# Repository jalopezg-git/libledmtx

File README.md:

# libledmtx: a library to drive LED dot-matrix displays written in PIC18 assembler

## Introduction
The libledmtx project was developed as a subproject of [p18clock](https://github.com/jalopezg-git/p18clock).
The library is completely written in PIC18 assembler and follows the call convention of the [SDCC](http://sdcc.sourceforge.net/) pic16 port.
Exported routines are meant to be called in by C code.
If you intend to issue calls from assembler, make sure that you follow the [pic16 port](http://sdcc.sourceforge.net/doc/sdccman.pdf) call convention.

## Building libledmtx
Before compiling the library make sure you have this installed:
- [gputils](https://gputils.sourceforge.io/) (the GNU PIC utilities), providing an assembler, librarian, and linker
- GNU make
- GNU gettext-runtime (provides `envsubst`)

To build libledmtx change to the directory where you extracted libledmtx and type
```bash
$ make

# To also compile the included examples
$ cd examples/
$ make
````

### Optional features
Additional features can be enabled / disabled by appending a list of `ENABLE_xxx=(0|1)` to the make command line, e.g. to build libledmtx with support for double buffer

```bash
$ make ENABLE_DOUBLE_BUFFER=1
```

#### Double buffer
libledmtx can be optionally built to support double buffer configuration.  To do so, you can append `ENABLE_DOUBLE_BUFFER=1` to the make command line.
Note that, in a double-buffer build, both the frontbuffer and backbuffer point to the same buffer by default.  See [`ledmtx_setbackbuffer()`](https://github.com/jalopezg-git/libledmtx/blob/master/include/ledmtx_core.h#L191) for details.

The feature is disabled by default.  Enabling it uses +4 additional bytes of RAM and makes each library function that touches a buffer +2 cycles slower, including the driver's vertical refresh routine.
This is, in general, acceptable for most applications though.

#### User-defined viewport
Set `ENABLE_VIEWPORT=1` to build a viewport-aware version of libledmtx, i.e. enable support for having a framebuffer larger than the physical display.
In this case, `libledmtx_init()` sets both, the framebuffer and initial viewport geometry.  The visible rectangle can be set as many times as needed via [`ledmtx_setviewport()`](https://github.com/jalopezg-git/libledmtx/blob/master/include/ledmtx_core.h#L147).

This feature is disabled by default.  When enabled, it uses +4 additional bytes of RAM in the access bank and makes the driver vertical refresh routine slightly slower (~5 cycles).

## Testing
The test suite is based on LLVM's lit.  Besides the dependencies required to build libledmtx, running tests also requires:
- llvm (provides `lit`)
- SDCC
- gpsim (The GNUPIC Simulator)

Tests can be simply run as follows:
```bash
$ lit tests/
```

## Installing
To install required files, change to the directory where you cloned libledmtx and run `make install` setting `INSTALL_PREFIX` to the destination directory, e.g.
```bash
$ make INSTALL_PREFIX=$HOME/.local/libledmtx/ install
```

## Hardware
Refer to docs and KiCad schematic design in the [hardware](https://github.com/jalopezg-git/libledmtx/tree/master/hardware/) directory.
The r393c164 driver requires a `ledmtx_r393c164.inc` configuration file that specifies which I/O port and pins to use for each output signal.
The used I/O port still should be manually configured writing to the `TRISx` / `ADCON1` registers.

## Examples
Some minimal examples are available in the [examples](https://github.com/jalopezg-git/libledmtx/tree/master/examples/) directory.
- [hello32x7](https://github.com/jalopezg-git/libledmtx/blob/master/examples/hello32x7/hello32x7.c), a simple program that prints "hello" using `printf()` (via the `STREAM_USER` stdio stream).
- [scrollstr32x7](https://github.com/jalopezg-git/libledmtx/blob/master/examples/scrollstr32x7/scrollstr32x7.c), that exercises the scrollstr module to asynchronously scroll a long text.

## How does it work?
libledmtx reserves part of the device's RAM as video memory (framebuffer).  The framebuffer is encoded left to right, top to bottom, 1bpp, i.e. each byte holds the value of 8 pixels.
The library has two distinct parts: a set of routines that alter the contents of the framebuffer, and the 'driver', which periodically reads (parts of) the framebuffer and changes the state of the appropriate MCU I/O pins in order to drive the simple video hardware (see [Hardware](https://github.com/jalopezg-git/libledmtx/#hardware)).
The driver is usually activated as part of the libledmtx interrupt service routine (ISR).

For the sake of efficiency, libledmtx tries to avoid using the `BSR` register where possible; thus, frequently accessed data is kept in the Access Bank.
Note that neither SDCC nor libledmtx support the PIC18 Extended Instruction Set (XINST).

libledmtx offers a [core](https://github.com/jalopezg-git/libledmtx/blob/master/include/ledmtx_core.h) set of routines (e.g. `ledmtx_putpixel()`, `ledmtx_setfont()`, or `ledmtx_putchar()`), and a set of modules that can be optionally linked in order to extend the core's capabilities.  Specifically, the following modules are supported:
- `scrollstr`: helper for character string scroll.  Allows automatic scroll of up to 8 strings from the ISR (see [`ledmtx_scrollstr_start()`](https://github.com/jalopezg-git/libledmtx/blob/master/include/ledmtx_scrollstr.h)).
- `perf`: measures time taken to service the libledmtx interrupt.

As of june 2024, libledmtx can work with multiple buffers (experimental).  In this configuration, the driver reads from the frontbuffer, whereas the framebuffer manipulation routines act on the backbuffer.  Once the backbuffer is ready, buffers can be swapped by using `ledmtx_swapbuffers()`.
In this case, buffers are pointed to by `ledmtx_frontbuffer` and `ledmtx_backbuffer`.  Given the additional level of indirection, all routines that need to load buffer addresses had the `lfsr` instruction replaced by two `movff` instructions, making them two cycles slower.  This overhead is, in general, acceptable for most of the purposes.

The addition of this feature also allows for changing the viewport, i.e. having a framebuffer larger than the actual display and only making part of it visible (TBD).

## Issues / limits
core:
- Maximum framebuffer size:	255x255
- Maximum size of a character:		8x255 (greater than VGA 8x14 is probably useless?)

r393c164 driver:
- High row count most probably looks dimmed, due to multiplexing.

scrollstr module:
- Auto-scroll vector capacity:		8 entries
- Maximum string length:		128 chars (including `\0`)

## Notes on linking against libledmtx
This section provides general guidelines to use and link libledmtx in your project.

1. Copy [`Makefile.template`](https://github.com/jalopezg-git/libledmtx/blob/master/doc/Makefile.template) to you project directory and tune it.
In particular, the value of the `P18FXXX`, `LIBDIR`, `INCLUDEDIR`, `O` and `modules` variables should be set accordingly.
`LIBDIR` and `INCLUDEDIR` should point to the libledmtx install directories.
`O` and `MODULES` list additional libledmtx objects and/or libraries that should be linked.
The `OBJECTS +=` line should list your project object files.

2. Write configuration file for the driver.
For the r393c164 driver, the file `ledmtx_r393c164.inc` (located in your project's directory), should look like this.  The I/O port and pins should be changed to reflect your wiring.
```
  LEDMTX_R393C164_IOPORT	equ	PORTA
  LEDMTX_R393C164_RCLK		equ	RA0
  LEDMTX_R393C164_RRST		equ	RA1
  LEDMTX_R393C164_RENA		equ	RA2
  LEDMTX_R393C164_CCLK		equ	RA3
  LEDMTX_R393C164_CDAT		equ	RA4
```

3. The `LEDMTX_BEGIN_MODULES_INIT` / `LEDMTX_END_MODULES_INIT` section is mandatory even if you are not using any module.
Header files for any module should be `#include`d before `ledmtx_core.h`.
A framebuffer (i.e., a small data memory area that stores the current frame) should be declared as follows:
```c
  LEDMTX_DECLARE_FRAMEBUFFER(_width, _height)
```
where `_width` and `_height` must be constant expressions.

4. If you are using TMR0 interrupts to call the driver-specific routine for vertical refresh, you should also include the following code:
```c
  DEF_INTLOW(low_int)
  DEF_HANDLER(SIG_TMR0, _tmr0_handler)
  END_DEF

  SIGHANDLERNAKED(_tmr0_handler)
  {
    LEDMTX_BEGIN_ISR
    LEDMTX_VERTREFRESH
    LEDMTX_END_ISR
  }
```

5. `ledmtx_init()` should be called before calling any other libledmtx function.
If Timer0 is used to drive the display (recommended), proper values for the `tmr0h`, `tmr0l`, and `t0con` paramaters have to be passed.
The `ledmtx_modegen` utility included in [support/](https://github.com/jalopezg-git/libledmtx/tree/master/support/) automates this task.
If you are using the provided `Makefile.template`, `ledmtx_modegen_modes.h` shall be automatically generated from the provided values.  Because the `LEDMTX__DEFAULT_xxx` preprocessor macros are also defined in the abovementioned header, the call to `ledmtx_init()` may just become:
```c
#include "ledmtx_modegen_modes.h"
// ...

ledmtx_init(LEDMTX_INIT_CLEAR | LEDMTX_INIT_TMR0,
	    LEDMTX__DEFAULT_WIDTH, LEDMTX__DEFAULT_HEIGHT,
	    LEDMTX__DEFAULT_TMR0H, LEDMTX__DEFAULT_TMR0L, LEDMTX__DEFAULT_T0CON);
```

## Contributing
Contributions either in the form of new features / fixes, hardware improvements, or documentation are welcome :+1:.
Feel free to open a pull request if you have something to say!

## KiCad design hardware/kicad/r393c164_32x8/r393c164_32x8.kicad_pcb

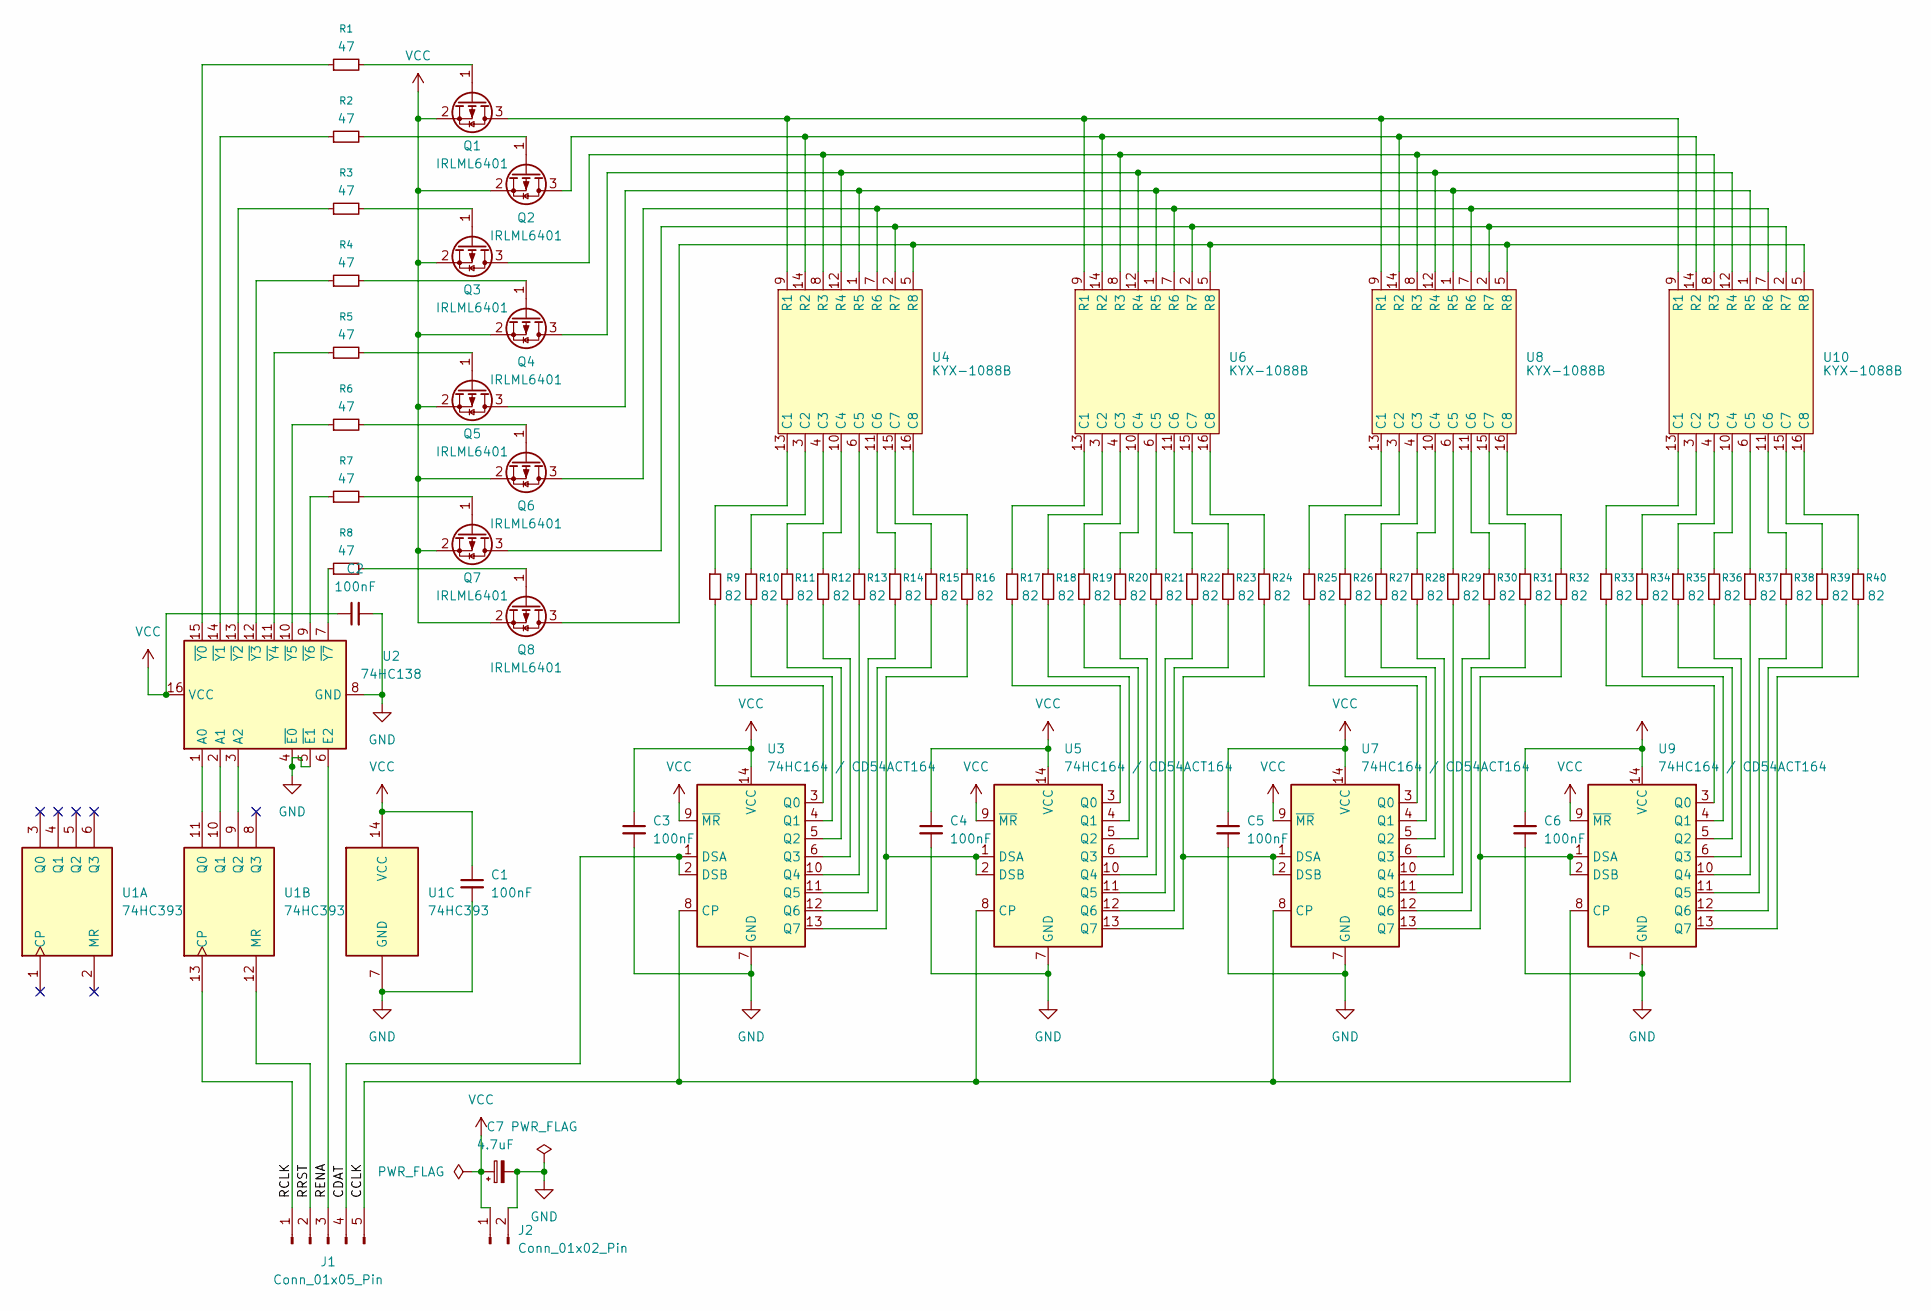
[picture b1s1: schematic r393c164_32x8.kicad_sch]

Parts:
C1, C2, C3, C4, C5, C6: 100nF; C_1206_3216Metric_Pad1.33x1.80mm_HandSolder
C7: 4.7uF; CP_Radial_D4.0mm_P2.00mm
J1: Conn_01x05_Pin; PinHeader_1x05_P2.54mm_Vertical
J2: Conn_01x02_Pin; PinHeader_1x02_P2.54mm_Vertical
Q1, Q2, Q3, Q4, Q5, Q6, Q7, Q8: IRLML6401; SOT-23
R1, R2, R3, R4, R5, R6, R7, R8: 47; R_0805_2012Metric_Pad1.20x1.40mm_HandSolder
R9, R10, R11, R12, R13, R14, R15, R16, R17, R18, R19, R20, R21, R22, R23, R24, R25, R26, R27, R28, R29, R30, R31, R32, R33, R34, R35, R36, R37, R38, R39, R40: 82; R_0805_2012Metric_Pad1.20x1.40mm_HandSolder
U1: 74HC393; SOIC-14_3.9x8.7mm_P1.27mm
U2: 74HC138; SOIC-16_3.9x9.9mm_P1.27mm
U3, U5, U7, U9: 74HC164 / CD54ACT164; SOIC-14_3.9x8.7mm_P1.27mm
U4, U6, U8, U10: KYX-1088B; KYX-1088AB

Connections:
/CCLK: J1.5, U3.8 (CP), U5.8 (CP), U7.8 (CP), U9.8 (CP)
/CDAT: J1.4, U3.1 (DSA), U3.2 (DSB)
/RCLK: J1.1, U1.13 (CP)
/RENA: J1.3, U2.6 (E2)
/RRST: J1.2, U1.12 (MR)
GND: C1.2, C2.2, C3.2, C4.2, C5.2, C6.2, C7.2, J2.2, U1.7 (GND), U2.4 (~E0), U2.5 (~E1), U2.8 (GND), U3.7 (GND), U5.7 (GND), U7.7 (GND), U9.7 (GND)
unnamed: Q1.3 (D), U4.9 (R1), U6.9 (R1), U8.9 (R1), U10.9 (R1)
unnamed: Q1.1 (G), R1.2
unnamed: Q2.3 (D), U4.14 (R2), U6.14 (R2), U8.14 (R2), U10.14 (R2)
unnamed: Q2.1 (G), R2.2
unnamed: Q3.3 (D), U4.8 (R3), U6.8 (R3), U8.8 (R3), U10.8 (R3)
unnamed: Q3.1 (G), R3.2
unnamed: Q4.3 (D), U4.12 (R4), U6.12 (R4), U8.12 (R4), U10.12 (R4)
unnamed: Q4.1 (G), R4.2
unnamed: Q5.3 (D), U4.1 (R5), U6.1 (R5), U8.1 (R5), U10.1 (R5)
unnamed: Q5.1 (G), R5.2
unnamed: Q6.3 (D), U4.7 (R6), U6.7 (R6), U8.7 (R6), U10.7 (R6)
unnamed: Q6.1 (G), R6.2
unnamed: Q7.3 (D), U4.2 (R7), U6.2 (R7), U8.2 (R7), U10.2 (R7)
unnamed: Q7.1 (G), R7.2
unnamed: Q8.3 (D), U4.5 (R8), U6.5 (R8), U8.5 (R8), U10.5 (R8)
unnamed: Q8.1 (G), R8.2
unnamed: U1.11 (Q0), U2.1 (A0)
unnamed: U1.10 (Q1), U2.2 (A1)
unnamed: U1.9 (Q2), U2.3 (A2)
unnamed: R1.1, U2.15 (~Y0)
unnamed: R2.1, U2.14 (~Y1)
unnamed: R3.1, U2.13 (~Y2)
unnamed: R4.1, U2.12 (~Y3)
unnamed: R5.1, U2.11 (~Y4)
unnamed: R6.1, U2.10 (~Y5)
unnamed: R7.1, U2.9 (~Y6)
unnamed: R8.1, U2.7 (~Y7)
unnamed: R9.2, U3.3 (Q0)
unnamed: R10.2, U3.4 (Q1)
unnamed: R11.2, U3.5 (Q2)
unnamed: R12.2, U3.6 (Q3)
unnamed: R13.2, U3.10 (Q4)
unnamed: R14.2, U3.11 (Q5)
unnamed: R15.2, U3.12 (Q6)
unnamed: R16.2, U3.13 (Q7), U5.1 (DSA), U5.2 (DSB)
unnamed: R9.1, U4.13 (C1)
unnamed: R10.1, U4.3 (C2)
unnamed: R11.1, U4.4 (C3)
unnamed: R12.1, U4.10 (C4)
unnamed: R13.1, U4.6 (C5)
unnamed: R14.1, U4.11 (C6)
unnamed: R15.1, U4.15 (C7)
unnamed: R16.1, U4.16 (C8)
unnamed: R17.2, U5.3 (Q0)
unnamed: R18.2, U5.4 (Q1)
unnamed: R19.2, U5.5 (Q2)
unnamed: R20.2, U5.6 (Q3)
unnamed: R21.2, U5.10 (Q4)
unnamed: R22.2, U5.11 (Q5)
unnamed: R23.2, U5.12 (Q6)
unnamed: R24.2, U5.13 (Q7), U7.1 (DSA), U7.2 (DSB)
unnamed: R17.1, U6.13 (C1)
unnamed: R18.1, U6.3 (C2)
unnamed: R19.1, U6.4 (C3)
unnamed: R20.1, U6.10 (C4)
unnamed: R21.1, U6.6 (C5)
unnamed: R22.1, U6.11 (C6)
unnamed: R23.1, U6.15 (C7)
unnamed: R24.1, U6.16 (C8)
unnamed: R25.2, U7.3 (Q0)
unnamed: R26.2, U7.4 (Q1)
unnamed: R27.2, U7.5 (Q2)
unnamed: R28.2, U7.6 (Q3)
unnamed: R29.2, U7.10 (Q4)
unnamed: R30.2, U7.11 (Q5)
unnamed: R31.2, U7.12 (Q6)
unnamed: R32.2, U7.13 (Q7), U9.1 (DSA), U9.2 (DSB)
unnamed: R25.1, U8.13 (C1)
unnamed: R26.1, U8.3 (C2)
unnamed: R27.1, U8.4 (C3)
unnamed: R28.1, U8.10 (C4)
unnamed: R29.1, U8.6 (C5)
unnamed: R30.1, U8.11 (C6)
unnamed: R31.1, U8.15 (C7)
unnamed: R32.1, U8.16 (C8)
unnamed: R33.2, U9.3 (Q0)
unnamed: R34.2, U9.4 (Q1)
unnamed: R35.2, U9.5 (Q2)
unnamed: R36.2, U9.6 (Q3)
unnamed: R37.2, U9.10 (Q4)
unnamed: R38.2, U9.11 (Q5)
unnamed: R39.2, U9.12 (Q6)
unnamed: R40.2, U9.13 (Q7)
unnamed: R33.1, U10.13 (C1)
unnamed: R34.1, U10.3 (C2)
unnamed: R35.1, U10.4 (C3)
unnamed: R36.1, U10.10 (C4)
unnamed: R37.1, U10.6 (C5)
unnamed: R38.1, U10.11 (C6)
unnamed: R39.1, U10.15 (C7)
unnamed: R40.1, U10.16 (C8)
VCC: C1.1, C2.1, C3.1, C4.1, C5.1, C6.1, C7.1, J2.1, Q1.2 (S), Q2.2 (S), Q3.2 (S), Q4.2 (S), Q5.2 (S), Q6.2 (S), Q7.2 (S), Q8.2 (S), U1.14 (VCC), U2.16 (VCC), U3.9 (~MR), U3.14 (VCC), U5.9 (~MR), U5.14 (VCC), U7.9 (~MR), U7.14 (VCC), U9.9 (~MR), U9.14 (VCC)

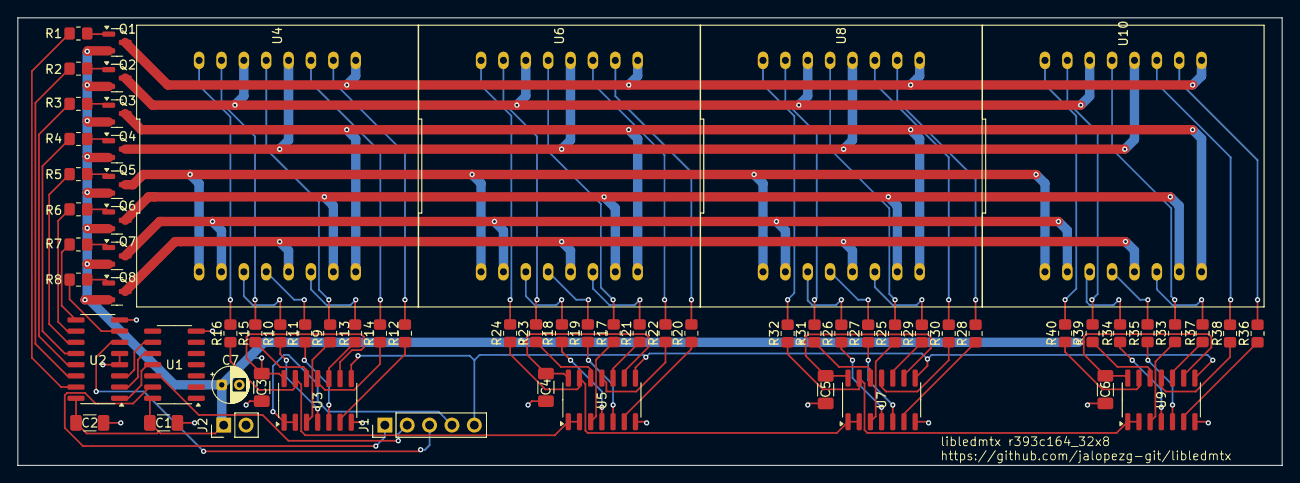
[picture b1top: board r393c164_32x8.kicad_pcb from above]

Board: 2 copper layers, 143.5 x 50.8 mm, 67 parts (0 on the bottom side), 98 nets.

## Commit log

2011-09-01 Legacy version of libledmtx, imported from old repository location
2011-09-01 Minor fix in README.md
2023-09-12 Improve documentation for files in `src/driver/`
2023-09-12 Improve documentation for files in `src/core/`
2023-09-12 Improve documentation for files in `src/font/`
2023-09-12 Improve documentation for files in `src/modules/`
2023-09-12 Improve documentation for files in `include/`
2023-09-12 Minor readability improvements on `ledmtx_tmr0config.c`
2023-09-12 Improve documentation for files in `examples/`
2023-09-12 Rename `ledmtx_scrollstr_s` to `ledmtx_scrollstr_desc`
2023-09-14 Check for `STACK_MODEL_LARGE` PP macro instead (unsupported)
2023-09-14 Add `--use-non-free` to CFLAGS
2023-10-25 Update COPYING (GNU Lesser GPL)
2024-04-08 README.md: add `How does it work?` section
2024-05-21 Add `.gitignore`
2024-05-24 Transition from `p18fxxx.inc` to `ledmtx_config.h`
    Deprecate `src/p18fxxx.inc` generated by make during build
    in favor of `include/ledmtx_config.h`, which contains additional
    information regarding the build.
    It is foreseen to include information regarding upcoming optional
    features, e.g. `LEDMTX_HAVE_DOUBLE_BUFFER`.
2024-05-24 [make.mk] Rename `AFLAGS` to `ASFLAGS`
2024-05-24 Add note about `BSR` and XINST in README.md
2024-05-27 [examples] Fix broken `__CONFIG` directive
2024-05-27 Apply minor fixes to `Makefile`s
2024-05-27 [tests] Add tests for driver
2024-05-27 Update `.gitignore`
2024-05-27 [tests] Add `lit` config files
2024-05-27 Add 'Testing' section to README.md
2024-05-27 [tests] Add SDCC integration tests
2024-05-27 [tests] Add tests for `perf` module
2024-05-27 [tests] Add tests for core routines
2024-05-27 [tests] Add tests for `scrollstr` module
2024-05-28 Move `_ledmtx_config_(tmr0h|tmr0l|t0con)` out of udata_acs
    Note that these are not required to be in the access RAM;
    access is always carried out via `movff`.
2024-05-28 [r393c164] Apply minor improvements
    * Optimize `OUTBIT`; shifting out a byte now requires 8 cycles less
2024-05-29 Apply optimizations to `ledmtx_scroll_(l|r)`
2024-06-02 [tests] Add double-buffer-specific tests
2024-06-03 Fix weird test failure in tests/core/setfont.S
    Apparently, gpsim confuses `_ledmtx_font_sz_w` and `_ledmtx_frontbuffer`
    when being asked to dump its content. This is most likely a bug in
    gpsim which should be reported (see below).
    Adjust CHECK line for now.
    ```
    /home/jalopezg/repos/libledmtx/tests/core/setfont.S:38:10: error: CHECK: expected string not found in input
2024-06-03 Workaround a bug in gpsim affecting r393c164 test
    Apparently, this test triggers a bug in gpsim; the effect of
    ```
    bsf LEDMTX_R393C164_IOPORT, LEDMTX_R393C164_RRST, A
    ```
    is not normally visible in the trace. However, setting a breakpoint
    seems to workaround the issue.
2024-06-03 Fix majority of unit tests for ENABLE_DOUBLE_BUFFER=1
2024-06-03 Expose `ledmtx_(front|back)buffer` pointers in ledmtx_core.h
2024-06-03 Copy also `*.inc` files when installing
2024-06-03 Use `LOAD_BUFADDR_IN_FSR0` throughout the library
    Use the `LOAD_BUFADDR_IN_FSR0` macro to load the address of the
    given buffer in FSR0. In single buffer builds, the address of
    `_ledmtx_framebuffer` is loaded regardless of the specified buffer.
2024-06-03 Expose `ENABLE_DOUBLE_BUFFER` build option
2024-06-03 [core] Add routines for double-buffer manipulation
    * `ledmtx_setbackbuffer()`
    * `ledmtx_swapbuffers()`
    * `ledmtx_swapbuffers_on_vsync()`
2024-06-07 Expose `ENABLE_VIEWPORT` build option
2024-06-07 [r393c164] Apply minor optimization
2024-06-07 Add library support for changing viewport
2024-06-07 [tests] Fix main r393c164 test
2024-06-07 [r393c164] Support user-defined viewport
2024-06-07 [tests] Add tests for viewport feature
2024-06-07 [tests] Add SCC integration test for scrollstr
2024-06-07 Fixed heading indentation in README.md
2024-12-16 [stdio] putchar: support '\r' (carriage ret)
2024-12-24 Update documentation for `ledmtx_modegen`
2024-12-24 [examples] Update examples to use the `ledmtx_modegen` utility
2024-12-24 [support] Replace legacy `ledmtx_tmr0config` by `ledmtx_modegen`
    `ledmtx_modegen` provides a more robust and flexible replacement
    for `ledmtx_tmr0config`. See usage.
2024-12-24 Simplify installation via `INSTALL_PREFIX` variable
2024-12-28 Define `LEDMTX_GITBRANCH` in ledmtx_config.h
2025-09-27 Add KiCad reference files for r393c164 (32x8)
2025-10-14 r393c164_32x8: Update KiCad schematic
    * Renamed references `U3` -- `U10`
    * Replaced P-channel MOSFET by `IRLML6401`
    * Added VCC + GND connector (`J2`)
2025-10-14 r393c164_32x8: Add reference PCB layout
2025-10-16 r393c164_32x8: fix defects in KiCad schematic / PCB
2025-11-22 include/ledmtx_r0reg_tblrd.h: fix linker error non-EEPROM devices
2025-11-22 [core] Introduce the `LEDMTX_DECLARE_FRAMEBUFFER()` PP macro
    `LEDMTX_DECLARE_FRAMEBUFFER(_width, _height)` yields a more user-friendly
    interface for declaring the framebuffer. `LEDMTX_FRAMEBUFFER_RES()` is
    now deprecated.
2025-11-22 [font] Add `libledmtx_font6x8.S`
    As part of this change, `include/ledmtx_font5x7.h` was renamed to
    `include/ledmtx_fontstd.h`. As of this commit, the latter file should
    be included instead.
2025-11-22 [scrollstr] Allow for user-specified height of the scroll region
    This is useful, e.g. in case the current font height is actually
    smaller than the intended region.
2025-12-08 [font] Minor fixes to `libledmtx_font6x8.S`
2025-12-08 [core] `ledmtx_setviewport()`: fix annoying blink after changing viewport
    `ledmtx_setviewport()` should reset current scanline to 0 only if
    it lies outside of the new viewport.
2025-12-08 [r393c164] Introduce experimental soft-PWM support
    This commit implements simple, experimental soft-PWM to skip some
    vertrefresh cycles. At this stage, it may not work properly, and
    thus it is not yet advertised / documented.
2026-01-24 [r393c164] Add experimental software-based PWM support
    This commit adds experimental software-based PWM support (requires an
    additional timer module; defaults to Timer3). User is reponsible for:
    - Manually configuring Timer3
    - Calling `___ledmtx_r393c164_E_softpwm_duty_end` on Timer3 overflow
    `___ledmtx_r393c164_E_softpwm_tmr3` may be adjusted to adjust PWM duty
    cycle. In particular, the less the distance to overflow (0xffff), the
2026-02-09 [doc] Update `README.md`
